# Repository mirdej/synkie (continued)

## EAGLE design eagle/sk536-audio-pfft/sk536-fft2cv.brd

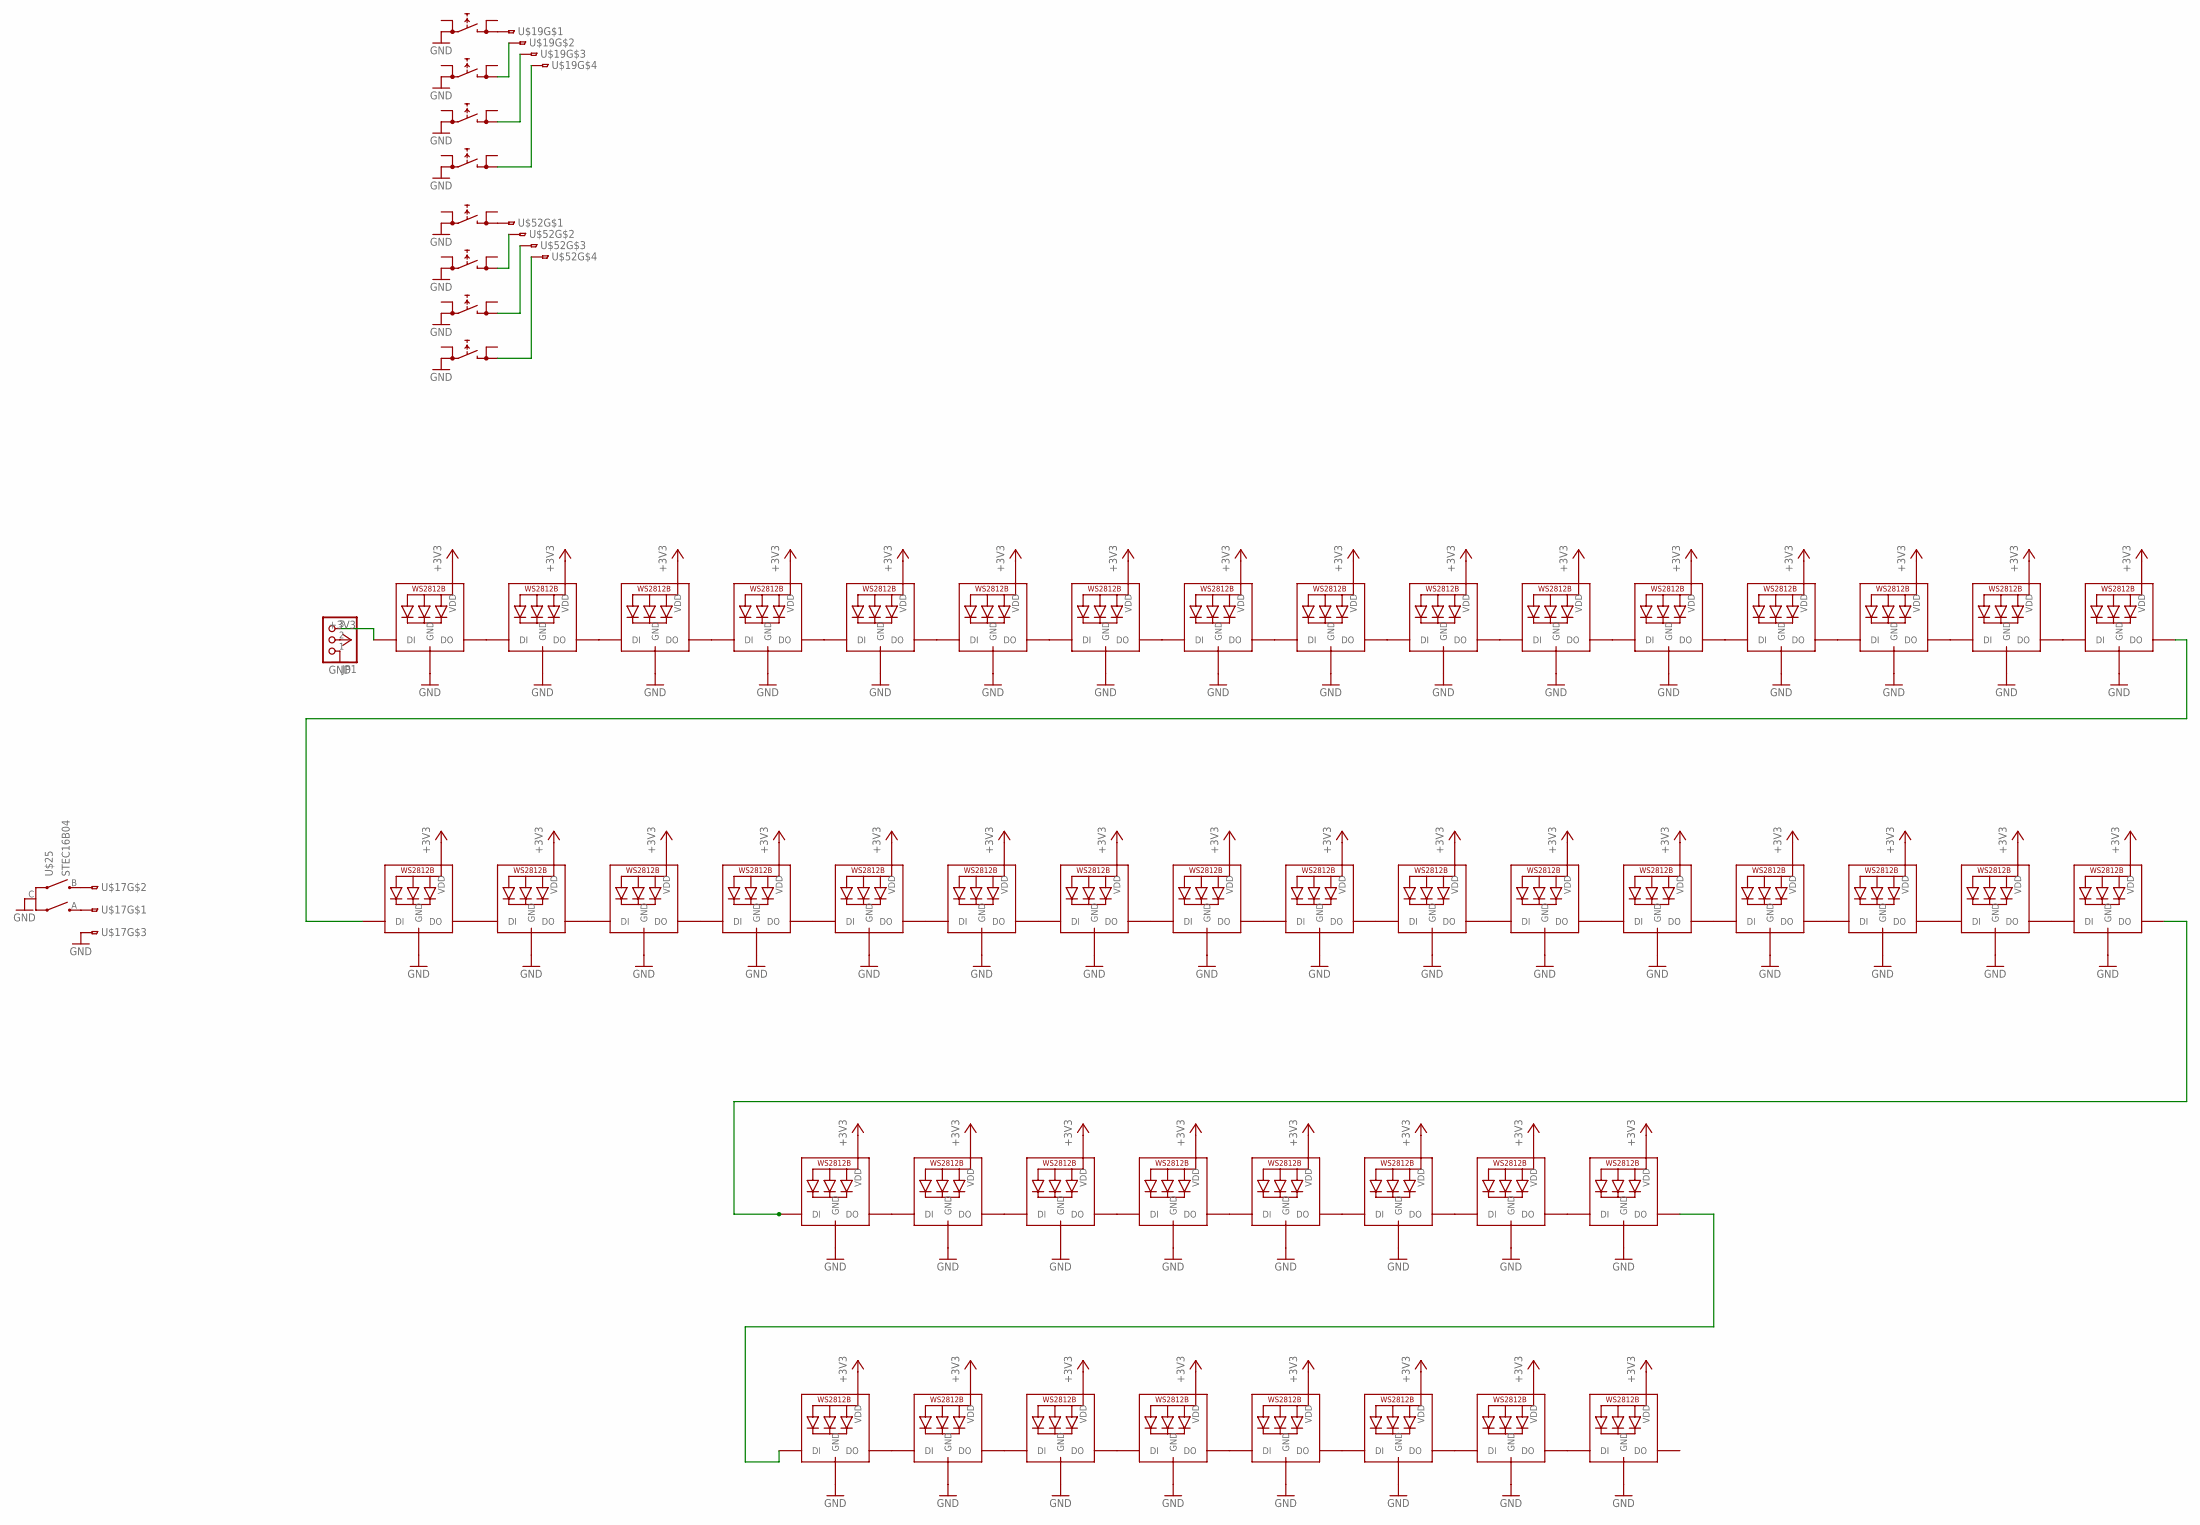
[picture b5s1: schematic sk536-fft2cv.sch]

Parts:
JP1: PINHD-1X3; 1X03
T1, T2, T3, T4, T5, T6, T7, T8: PRINTTASTER_SMDALPS-SKQ; SKQGAKE010
U$1, U$2, U$3, U$4, U$5, U$6, U$7, U$8, U$9, U$10, U$11, U$12, U$13, U$14, U$15, U$16, U$18, U$20, U$21, U$22, U$23, U$24, U$26, U$27, U$28, U$29, U$30, U$31, U$32, U$33, U$34, U$35, U$36, U$37, U$38, U$39, U$40, U$41, U$42, U$43, U$44, U$45, U$46, U$47, U$48, U$49, U$50, U$51: SK6812MINI
U$17: 3PIN-SMD-2.54
U$19, U$52: 4PIN-SMD; 4PIN-SMD-2.54
U$25: STEC16B04

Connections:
+3V3: JP1.2, U$1.4 (VDD), U$2.4 (VDD), U$3.4 (VDD), U$4.4 (VDD), U$5.4 (VDD), U$6.4 (VDD), U$7.4 (VDD), U$8.4 (VDD), U$9.4 (VDD), U$10.4 (VDD), U$11.4 (VDD), U$12.4 (VDD), U$13.4 (VDD), U$14.4 (VDD), U$15.4 (VDD), U$16.4 (VDD), U$18.4 (VDD), U$20.4 (VDD), U$21.4 (VDD), U$22.4 (VDD), U$23.4 (VDD), U$24.4 (VDD), U$26.4 (VDD), U$27.4 (VDD), U$28.4 (VDD), U$29.4 (VDD), U$30.4 (VDD), U$31.4 (VDD), U$32.4 (VDD), U$33.4 (VDD), U$34.4 (VDD), U$35.4 (VDD), U$36.4 (VDD), U$37.4 (VDD), U$38.4 (VDD), U$39.4 (VDD), U$40.4 (VDD), U$41.4 (VDD), U$42.4 (VDD), U$43.4 (VDD), U$44.4 (VDD), U$45.4 (VDD), U$46.4 (VDD), U$47.4 (VDD), U$48.4 (VDD), U$49.4 (VDD), U$50.4 (VDD), U$51.4 (VDD)
GND: JP1.1, T1.2 (0), T2.2 (0), T3.2 (0), T4.2 (0), T5.2 (0), T6.2 (0), T7.2 (0), T8.2 (0), U$1.2 (GND), U$2.2 (GND), U$3.2 (GND), U$4.2 (GND), U$5.2 (GND), U$6.2 (GND), U$7.2 (GND), U$8.2 (GND), U$9.2 (GND), U$10.2 (GND), U$11.2 (GND), U$12.2 (GND), U$13.2 (GND), U$14.2 (GND), U$15.2 (GND), U$16.2 (GND), U$17.3, U$18.2 (GND), U$20.2 (GND), U$21.2 (GND), U$22.2 (GND), U$23.2 (GND), U$24.2 (GND), U$25.C, U$26.2 (GND), U$27.2 (GND), U$28.2 (GND), U$29.2 (GND), U$30.2 (GND), U$31.2 (GND), U$32.2 (GND), U$33.2 (GND), U$34.2 (GND), U$35.2 (GND), U$36.2 (GND), U$37.2 (GND), U$38.2 (GND), U$39.2 (GND), U$40.2 (GND), U$41.2 (GND), U$42.2 (GND), U$43.2 (GND), U$44.2 (GND), U$45.2 (GND), U$46.2 (GND), U$47.2 (GND), U$48.2 (GND), U$49.2 (GND), U$50.2 (GND), U$51.2 (GND)
unnamed: U$1.1 (DO), U$2.3 (DI)
unnamed: U$2.1 (DO), U$3.3 (DI)
unnamed: U$3.1 (DO), U$4.3 (DI)
unnamed: U$4.1 (DO), U$5.3 (DI)
unnamed: U$5.1 (DO), U$6.3 (DI)
unnamed: U$6.1 (DO), U$7.3 (DI)
unnamed: U$7.1 (DO), U$8.3 (DI)
unnamed: U$8.1 (DO), U$9.3 (DI)
unnamed: U$9.1 (DO), U$10.3 (DI)
unnamed: U$10.1 (DO), U$11.3 (DI)
unnamed: U$13.1 (DO), U$14.3 (DI)
unnamed: U$14.1 (DO), U$15.3 (DI)
unnamed: U$15.1 (DO), U$16.3 (DI)
unnamed: U$11.1 (DO), U$12.3 (DI)
unnamed: U$12.1 (DO), U$13.3 (DI)
unnamed: U$26.1 (DO), U$27.3 (DI)
unnamed: U$27.1 (DO), U$28.3 (DI)
unnamed: U$28.1 (DO), U$29.3 (DI)
unnamed: U$29.1 (DO), U$30.3 (DI)
unnamed: U$30.1 (DO), U$31.3 (DI)
unnamed: U$31.1 (DO), U$32.3 (DI)
unnamed: U$32.1 (DO), U$33.3 (DI)
unnamed: U$33.1 (DO), U$34.3 (DI)
unnamed: U$34.1 (DO), U$35.3 (DI)
unnamed: U$35.1 (DO), U$36.3 (DI)
unnamed: U$38.1 (DO), U$39.3 (DI)
unnamed: U$39.1 (DO), U$40.3 (DI)
unnamed: U$40.1 (DO), U$41.3 (DI)
unnamed: U$36.1 (DO), U$37.3 (DI)
unnamed: U$37.1 (DO), U$38.3 (DI)
unnamed: U$16.1 (DO), U$26.3 (DI)
unnamed: U$18.3 (DI), U$41.1 (DO)
unnamed: U$18.1 (DO), U$20.3 (DI)
unnamed: U$20.1 (DO), U$21.3 (DI)
unnamed: U$23.1 (DO), U$24.3 (DI)
unnamed: U$24.1 (DO), U$42.3 (DI)
unnamed: U$42.1 (DO), U$43.3 (DI)
unnamed: U$21.1 (DO), U$22.3 (DI)
unnamed: U$22.1 (DO), U$23.3 (DI)
unnamed: U$17.1, U$25.A
unnamed: U$44.1 (DO), U$45.3 (DI)
unnamed: U$45.1 (DO), U$46.3 (DI)
unnamed: U$48.1 (DO), U$49.3 (DI)
unnamed: U$49.1 (DO), U$50.3 (DI)
unnamed: U$50.1 (DO), U$51.3 (DI)
unnamed: U$46.1 (DO), U$47.3 (DI)
unnamed: U$47.1 (DO), U$48.3 (DI)
unnamed: U$43.1 (DO), U$44.3 (DI)
unnamed: U$17.2, U$25.B
unnamed: JP1.3, U$1.3 (DI)
unnamed: T1.4 (1), U$19.1
unnamed: T2.4 (1), U$19.2
unnamed: T3.4 (1), U$19.3
unnamed: T4.4 (1), U$19.4
unnamed: T5.4 (1), U$52.1
unnamed: T6.4 (1), U$52.2
unnamed: T7.4 (1), U$52.3
unnamed: T8.4 (1), U$52.4

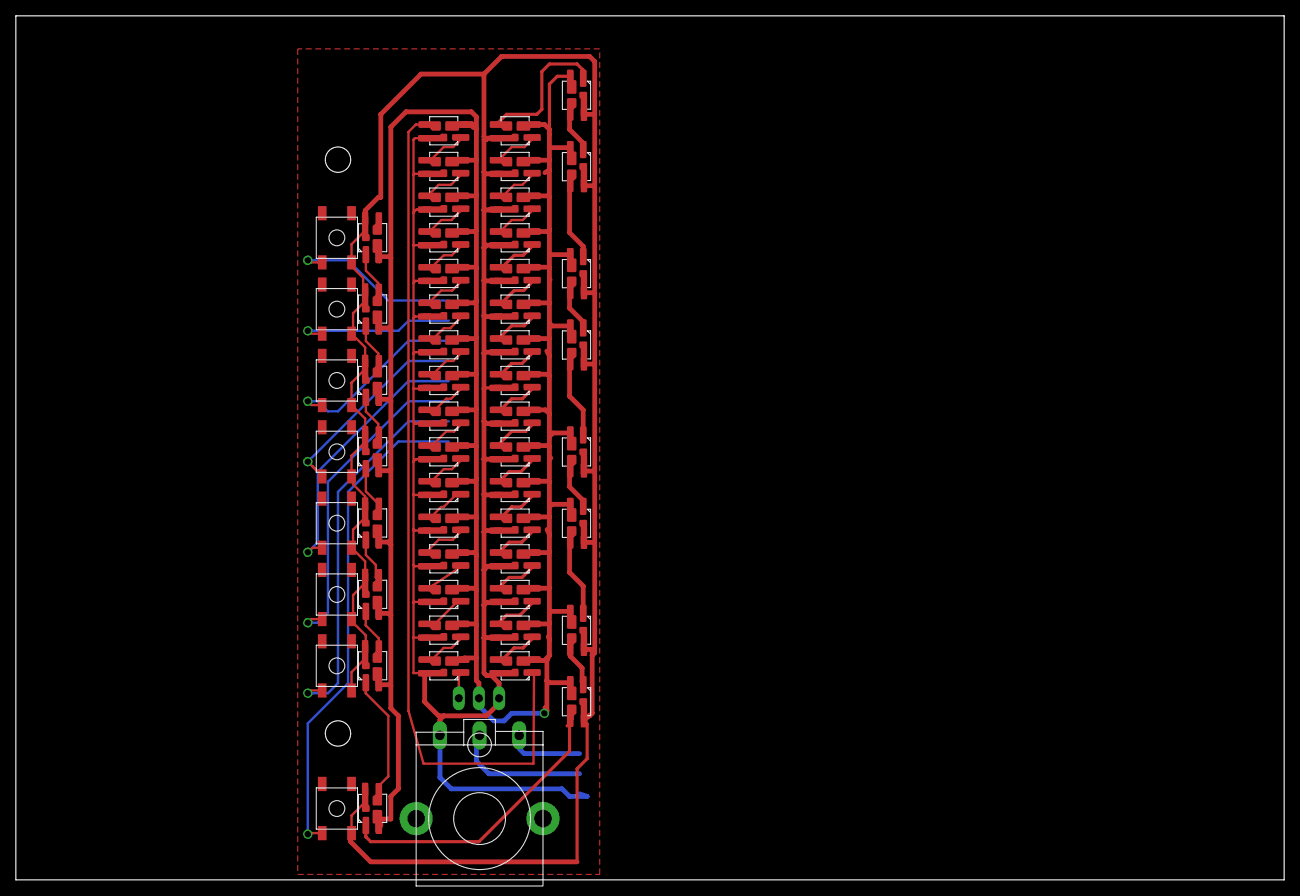
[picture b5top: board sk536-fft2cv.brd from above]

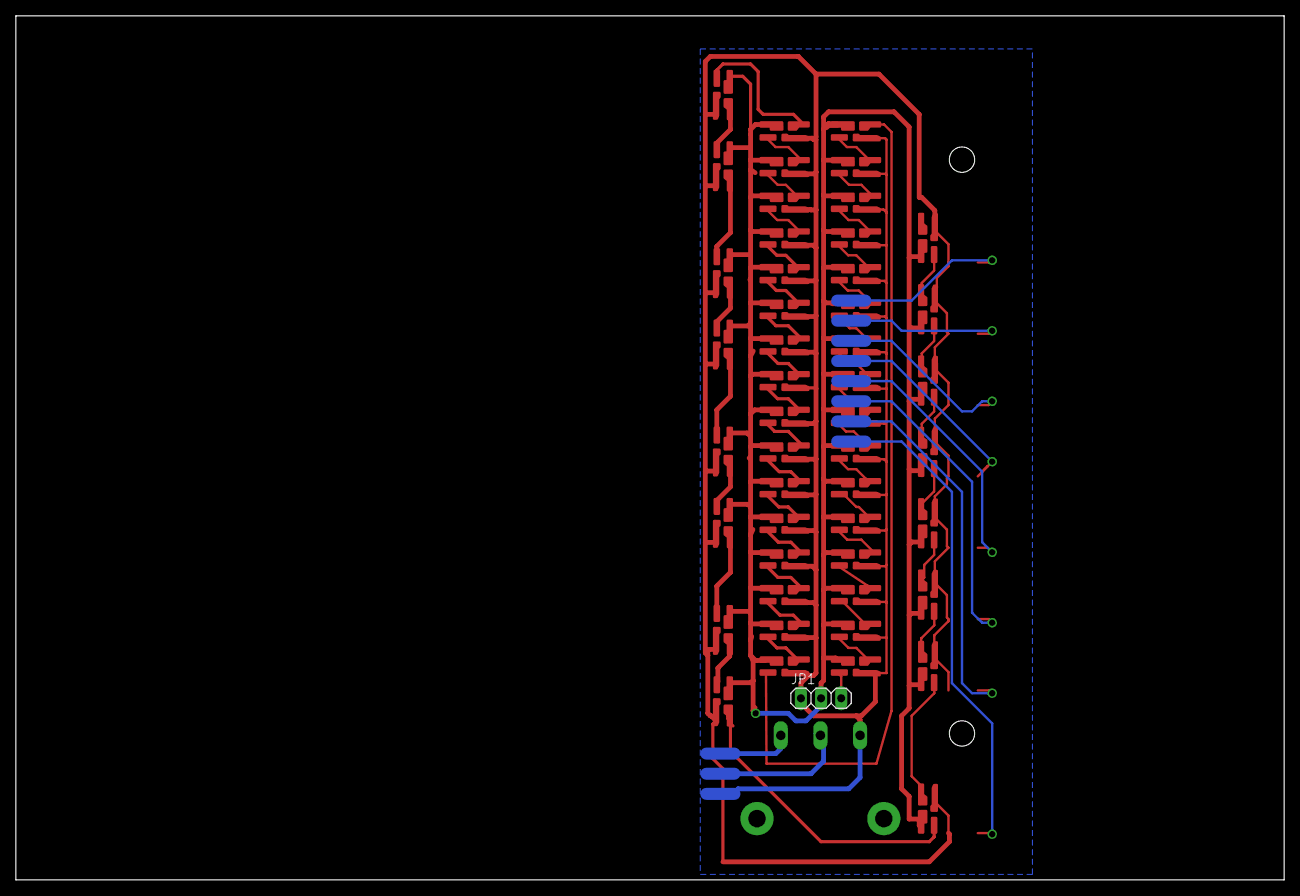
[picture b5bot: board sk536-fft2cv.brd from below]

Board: 2 copper layers, 160.0 x 109.0 mm, 61 parts (4 on the bottom side), 60 nets.

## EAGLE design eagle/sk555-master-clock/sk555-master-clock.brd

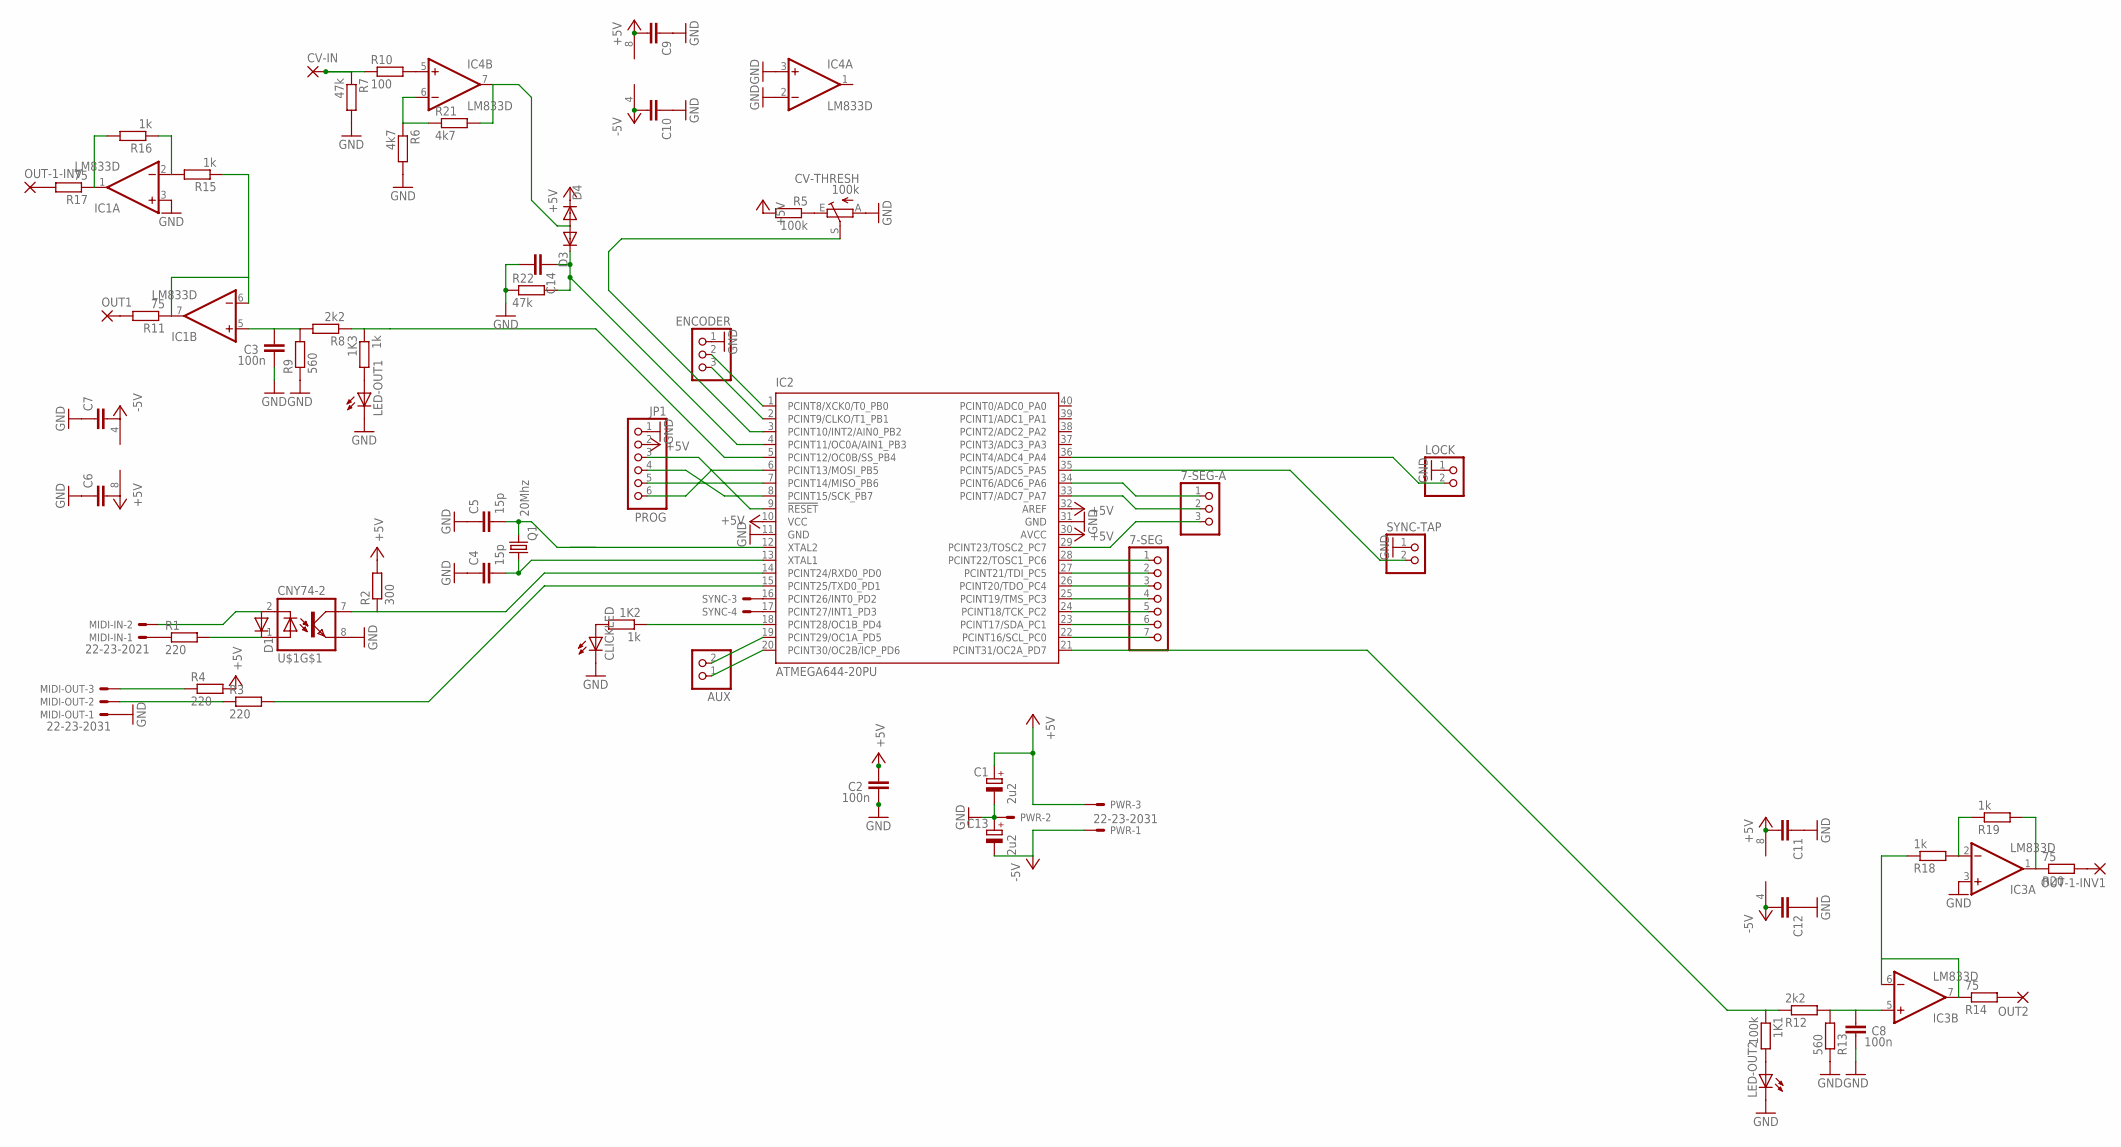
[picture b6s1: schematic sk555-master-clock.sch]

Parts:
1K1: 100k; R1206
1K2, 1K3: 1k; R1206
7-SEG: PINHD-1X7; 1X07
7-SEG-A: PINHD-1X3; 1X03
AUX: PINHD-1X2; 1X02
C1, C13: 2u2; CT3528
C2, C3, C8: 100n; C0805
C4, C5: 15p; C1206
C6, C7, C9, C10, C14: C-EUC1206; C1206
C11, C12: C-EUC0805; C0805
CLICKLED: LED3MM
CV-IN: 3,17/1,1
CV-THRESH: 100k; CIP20C-6MM
D1, D3, D4: DIODE-MINIMELF; MINIMELF
ENCODER: PINHD-1X3; 1X03
IC1, IC3, IC4: LM833D; SO08
IC2: ATMEGA644-20PU; DIL40
JP1: PROG; 1X06
LED-OUT1, LED-OUT2: LED3MM
LOCK: PINHD-1X2; 1X02
MIDI-IN: 22-23-2021
MIDI-OUT: 22-23-2031
OUT1, OUT2: 3,17/1,1
OUT-1-INV, OUT-1-INV1: 3,17/1,1
PWR: 22-23-2031
Q1: 20Mhz; HC49UP
R1, R3, R4: 220; R1206
R2: 300; R1206
R5: 100k; R1206
R6, R21: 4k7; R1206
R7, R22: 47k; R1206
R8, R12: 2k2; R1206
R9, R13: 560; R1206
R10: 100; R1206
R11, R14, R17, R20: 75; R1206
R15, R16, R18, R19: 1k; R1206
SYNC: 22-23-2041
SYNC-TAP: PINHD-1X2; 1X02
U$1: CNY74-2; DIL08

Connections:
+5V: C1.+, C2.1, C6.2, C9.2, C11.2, D4.C, IC1.8 (V+), IC2.10 (VCC), IC2.30 (AVCC), IC2.32 (AREF), IC3.8 (V+), IC4.8 (V+), JP1.2, PWR.3, R2.2, R4.2, R5.2
-5V: C7.2, C10.2, C12.2, C13.-, IC1.4 (V-), IC3.4 (V-), IC4.4 (V-), PWR.1
GND: C1.-, C2.2, C3.2, C4.1, C5.1, C6.1, C7.1, C8.2, C9.1, C10.1, C11.1, C12.1, C13.+, C14.2, CLICKLED.K (C), CV-THRESH.A, ENCODER.1, IC1.3 (+IN), IC2.11 (GND), IC2.31 (GND), IC3.3 (+IN), IC4.2 (-IN), IC4.3 (+IN), JP1.1, LED-OUT1.K (C), LED-OUT2.K (C), LOCK.1, MIDI-OUT.1, PWR.2, R6.2, R7.2, R9.1, R13.1, R22.1, SYNC-TAP.1, U$1.8 (EMI)
unnamed: IC2.8 (PCINT15/SCK_PB7), JP1.4
unnamed: IC2.7 (PCINT14/MISO_PB6), JP1.5
unnamed: IC2.6 (PCINT13/MOSI_PB5), JP1.6
unnamed: IC2.9 (!RESET), JP1.3
unnamed: C4.2, IC2.13 (XTAL1), Q1.1
unnamed: MIDI-IN.1, R1.1
unnamed: D1.A, MIDI-IN.2, U$1.2 (C)
unnamed: D1.C, R1.2, U$1.1 (A)
unnamed: IC2.14 (PCINT24/RXD0_PD0), R2.1, U$1.7 (COL)
unnamed: MIDI-OUT.2, R3.1
unnamed: MIDI-OUT.3, R4.1
unnamed: IC2.15 (PCINT25/TXD0_PD1), R3.2
unnamed: CV-IN.1, R7.1, R10.1
unnamed: OUT-1-INV.1, R17.2
unnamed: CV-THRESH.S, IC2.3 (PCINT10/INT2/AIN0_PB2)
unnamed: CV-THRESH.E, R5.1
unnamed: C14.1, D3.C, IC2.4 (PCINT11/OC0A/AIN1_PB3), R22.2
unnamed: OUT1.1, R11.2
unnamed: IC4.5 (+IN), R10.2
unnamed: IC4.6 (-IN), R6.1, R21.1
unnamed: IC2.36 (PCINT4/ADC4_PA4), LOCK.2
unnamed: IC2.35 (PCINT5/ADC5_PA5), SYNC-TAP.2
unnamed: 1K3.1, IC2.5 (PCINT12/OC0B/SS_PB4), R8.1
unnamed: OUT-1-INV1.1, R20.2
unnamed: 1K3.2, LED-OUT1.A
unnamed: IC2.16 (PCINT26/INT0_PD2), SYNC.3
unnamed: IC2.17 (PCINT27/INT1_PD3), SYNC.4
unnamed: IC1.2 (-IN), R15.2, R16.1
unnamed: C3.1, IC1.5 (+IN), R8.2, R9.2
unnamed: IC1.6 (-IN), IC1.7 (OUT), R11.1, R15.1
unnamed: 1K1.1, IC2.21 (PCINT31/OC2A_PD7), R12.1
unnamed: OUT2.1, R14.2
unnamed: 7-SEG.1, IC2.28 (PCINT22/TOSC1_PC6)
unnamed: C8.1, IC3.5 (+IN), R12.2, R13.2
unnamed: IC3.6 (-IN), IC3.7 (OUT), R14.1, R18.1
unnamed: C5.2, IC2.12 (XTAL2), Q1.2
unnamed: 1K1.2, LED-OUT2.A
unnamed: IC3.2 (-IN), R18.2, R19.1
unnamed: IC3.1 (OUT), R19.2, R20.1
unnamed: 7-SEG.2, IC2.27 (PCINT21/TDI_PC5)
unnamed: 7-SEG.3, IC2.26 (PCINT20/TDO_PC4)
unnamed: 7-SEG.4, IC2.25 (PCINT19/TMS_PC3)
unnamed: 7-SEG.5, IC2.24 (PCINT18/TCK_PC2)
unnamed: 7-SEG.6, IC2.23 (PCINT17/SDA_PC1)
unnamed: 7-SEG.7, IC2.22 (PCINT16/SCL_PC0)
unnamed: 7-SEG-A.3, IC2.29 (PCINT23/TOSC2_PC7)
unnamed: 7-SEG-A.2, IC2.33 (PCINT7/ADC7_PA7)
unnamed: 7-SEG-A.1, IC2.34 (PCINT6/ADC6_PA6)
unnamed: 1K2.2, CLICKLED.A
unnamed: 1K2.1, IC2.18 (PCINT28/OC1B_PD4)
unnamed: AUX.1, IC2.20 (PCINT30/OC2B/ICP_PD6)
unnamed: AUX.2, IC2.19 (PCINT29/OC1A_PD5)
unnamed: ENCODER.2, IC2.1 (PCINT8/XCK0/T0_PB0)
unnamed: ENCODER.3, IC2.2 (PCINT9/CLKO/T1_PB1)
unnamed: D3.A, D4.A, IC4.7 (OUT), R21.2
unnamed: IC1.1 (OUT), R16.2, R17.1

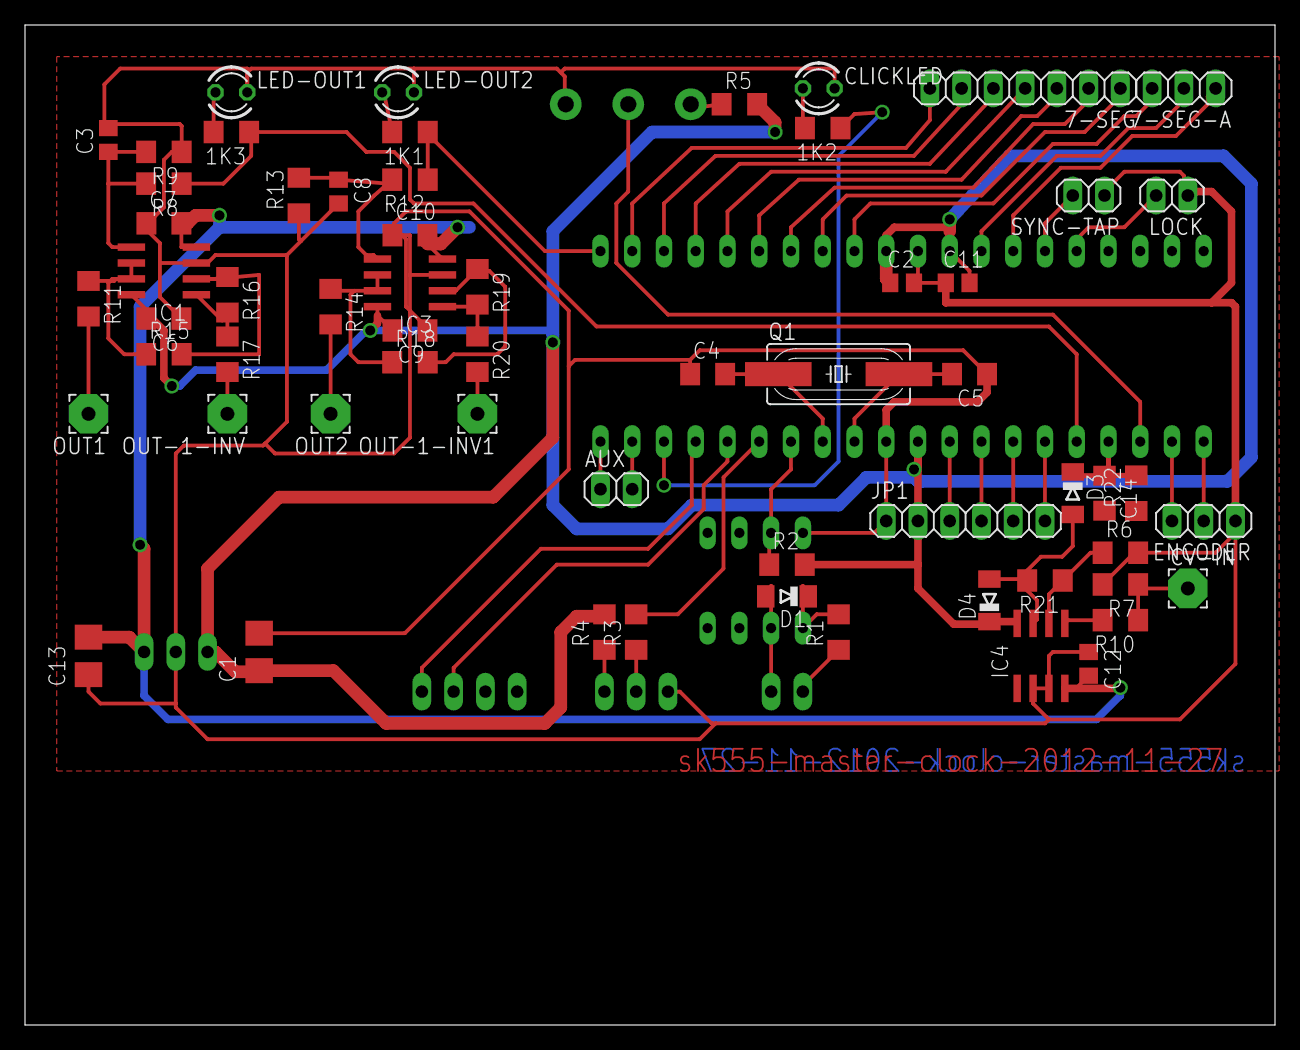
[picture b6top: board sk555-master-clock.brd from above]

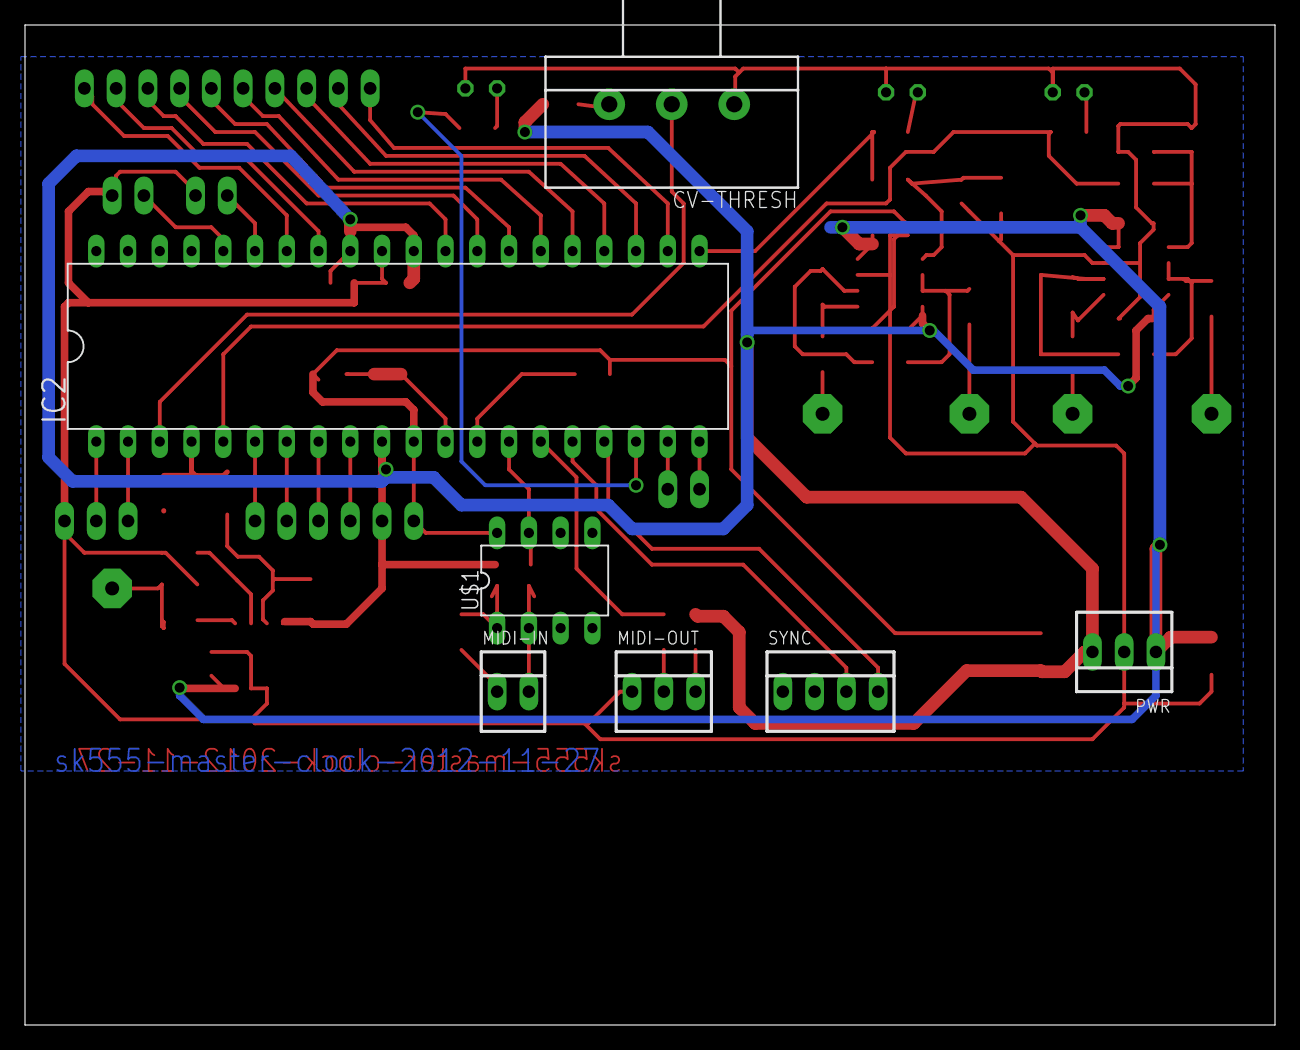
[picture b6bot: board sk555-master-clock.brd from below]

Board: 2 copper layers, 100.0 x 80.0 mm, 68 parts (7 on the bottom side), 59 nets.

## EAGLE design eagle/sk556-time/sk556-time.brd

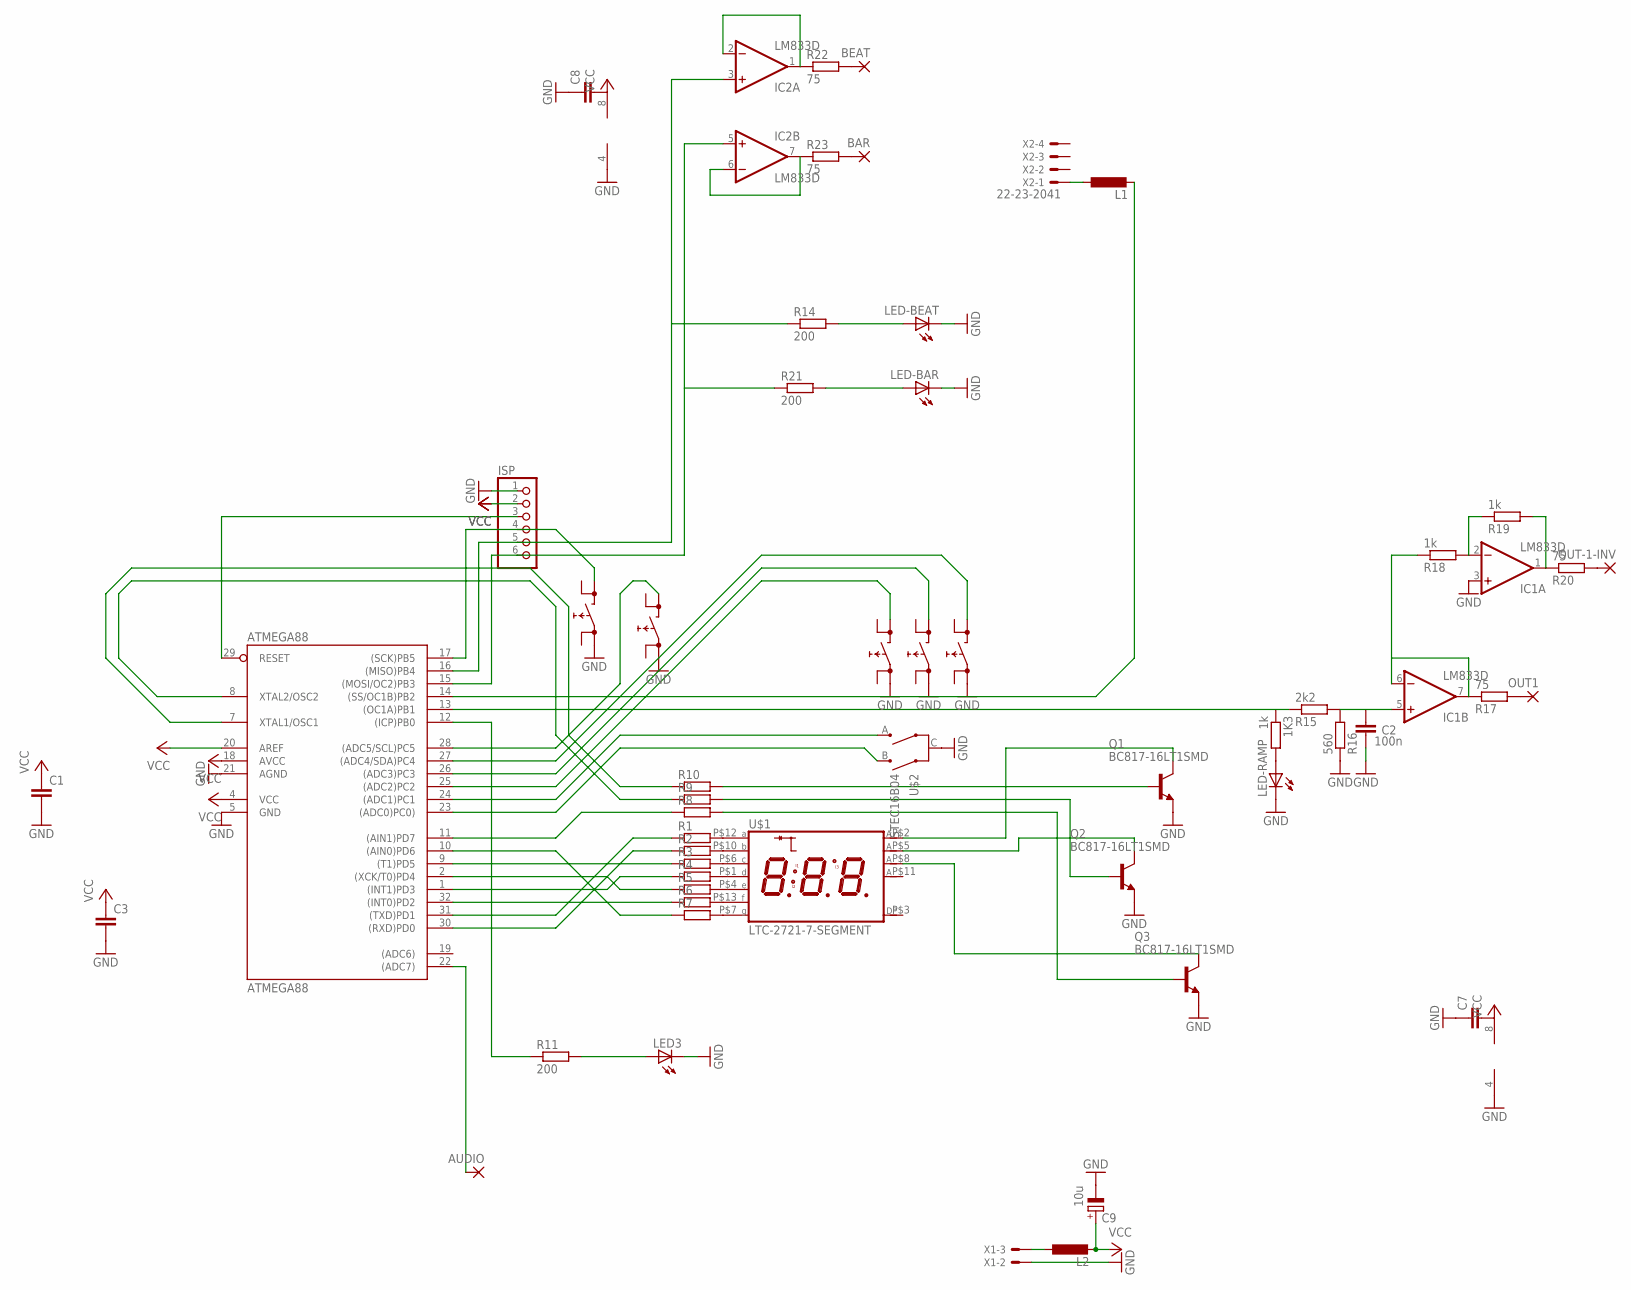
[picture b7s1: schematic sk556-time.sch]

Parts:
1K3: 1k; R1206
ATMEGA88: ATMEGA88; TQFP32-08
AUDIO: 3,17/1,1
BAR: 3,17/1,1
BEAT: 3,17/1,1
C1, C3, C7: C-EUC0603; C0603
C2: 100n; C0805
C8: C-EUC1206; C1206
C9: 10u; CT3528
IC1, IC2: LM833D; SO08
ISP: PINHD-1X6; 1X06
L1, L2: L-EUL5038P; L5038P
LED3: LEDCHIPLED_1206; CHIPLED_1206
LED-BAR: LEDCHIPLED_1206; CHIPLED_1206
LED-BEAT: LEDCHIPLED_1206; CHIPLED_1206
LED-RAMP: LEDCHIPLED_1206; CHIPLED_1206
LEFT: PRINTTASTER_SMD; SMD_SWITCH
LOOPER: PRINTTASTER_SMD; SMD_SWITCH
MIDDLE: PRINTTASTER_SMD; SMD_SWITCH
OUT1: 3,17/1,1
OUT-1-INV: 3,17/1,1
Q1, Q2, Q3: BC817-16LT1SMD; SOT23-BEC
R1, R2, R3, R4, R5, R6, R7, R8, R9, R10: R-EU_R1206; R1206
R11, R14, R21: 200; R1206
R15: 2k2; R1206
R16: 560; R1206
R17, R20, R22, R23: 75; R1206
R18, R19: 1k; R1206
RIGHT: PRINTTASTER_SMD; SMD_SWITCH
TAP: PRINTTASTER_SMD; SMD_SWITCH
U$1: LTC-2721-7-SEGMENT; LTC-2721
U$2: STEC16B04
X1: 22-23-2031
X2: 22-23-2041

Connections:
GND: ATMEGA88.5 (GND), ATMEGA88.21 (AGND), C1.2, C2.2, C3.2, C7.1, C8.1, C9.-, IC1.3 (+IN), IC1.4 (V-), IC2.4 (V-), ISP.1, LED3.C, LED-BAR.C, LED-BEAT.C, LED-RAMP.C, LEFT.AA (0), LOOPER.AA (0), MIDDLE.AA (0), Q1.E, Q2.E, Q3.E, R16.1, RIGHT.AA (0), TAP.AA (0), U$2.C, X1.2
MISO: ATMEGA88.16 ((MISO)PB4), IC2.3 (+IN), ISP.5, R14.1
MOSI: ATMEGA88.15 ((MOSI/OC2)PB3), IC2.5 (+IN), ISP.6, R21.1
unnamed: ATMEGA88.30 ((RXD)PD0), R2.1
unnamed: ATMEGA88.31 ((TXD)PD1), R1.1
unnamed: ATMEGA88.32 ((INT0)PD2), R6.1
unnamed: ATMEGA88.1 ((INT1)PD3), R4.1
unnamed: ATMEGA88.2 ((XCK/T0)PD4), R5.1
unnamed: ATMEGA88.8 (XTAL2/OSC2), R9.1
unnamed: ATMEGA88.7 (XTAL1/OSC1), R10.1
unnamed: ATMEGA88.11 ((AIN1)PD7), R8.1
unnamed: ATMEGA88.9 ((T1)PD5), R3.1
unnamed: R1.2, U$1.P$12 (A)
unnamed: R2.2, U$1.P$10 (B)
unnamed: R3.2, U$1.P$6 (C)
unnamed: R4.2, U$1.P$1 (D)
unnamed: R5.2, U$1.P$4 (E)
unnamed: R6.2, U$1.P$13 (F)
unnamed: R7.2, U$1.P$7 (G)
unnamed: ATMEGA88.29 (RESET), ISP.3
unnamed: ATMEGA88.22 ((ADC7)), AUDIO.1
unnamed: C7.2, IC1.8 (V+)
unnamed: ATMEGA88.14 ((SS/OC1B)PB2), L1.2
unnamed: L1.1, X2.1
unnamed: ATMEGA88.10 ((AIN0)PD6), R7.1
unnamed: ATMEGA88.23 ((ADC0)PC0)), U$2.B
unnamed: ATMEGA88.24 ((ADC1)PC1), U$2.A
unnamed: Q1.B, R10.2
unnamed: Q2.B, R9.2
unnamed: Q3.B, R8.2
unnamed: Q1.C, U$1.P$2 (D1)
unnamed: Q2.C, U$1.P$5 (D2)
unnamed: Q3.C, U$1.P$8 (D3)
unnamed: ATMEGA88.25 ((ADC2)PC2), RIGHT.BB (1)
unnamed: ATMEGA88.26 ((ADC3)PC3), MIDDLE.BB (1)
unnamed: ATMEGA88.27 ((ADC4/SDA)PC4), LEFT.BB (1)
unnamed: LED-BEAT.A, R14.2
unnamed: ATMEGA88.28 ((ADC5/SCL)PC5), LOOPER.BB (1)
unnamed: ATMEGA88.12 ((ICP)PB0), R11.1
unnamed: LED-BAR.A, R21.2
unnamed: IC2.1 (OUT), IC2.2 (-IN), R22.1
unnamed: 1K3.1, ATMEGA88.13 ((OC1A)PB1), R15.1
unnamed: C2.1, IC1.5 (+IN), R15.2, R16.2
unnamed: IC1.6 (-IN), IC1.7 (OUT), R17.1, R18.1
unnamed: 1K3.2, LED-RAMP.A
unnamed: IC1.2 (-IN), R18.2, R19.1
unnamed: OUT-1-INV.1, R20.2
unnamed: OUT1.1, R17.2
unnamed: BEAT.1, R22.2
unnamed: IC2.6 (-IN), IC2.7 (OUT), R23.1
unnamed: BAR.1, R23.2
unnamed: L2.1, X1.3
unnamed: IC1.1 (OUT), R19.2, R20.1
unnamed: LED3.A, R11.2
SCK: ATMEGA88.17 ((SCK)PB5), ISP.4, TAP.BB (1)
VCC: ATMEGA88.4 (VCC), ATMEGA88.18 (AVCC), ATMEGA88.20 (AREF), C1.1, C3.1, C8.2, C9.+, IC2.8 (V+), ISP.2, L2.2

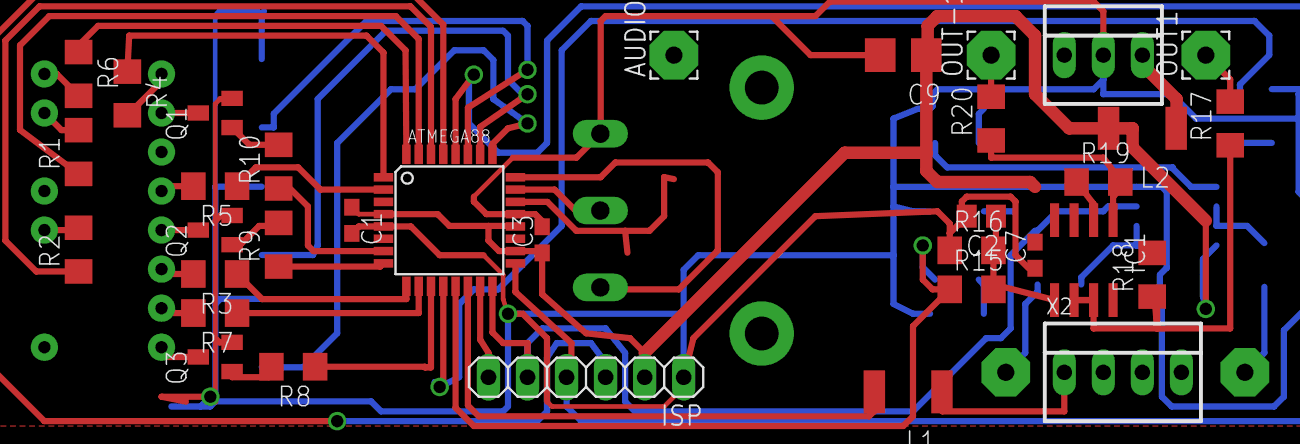
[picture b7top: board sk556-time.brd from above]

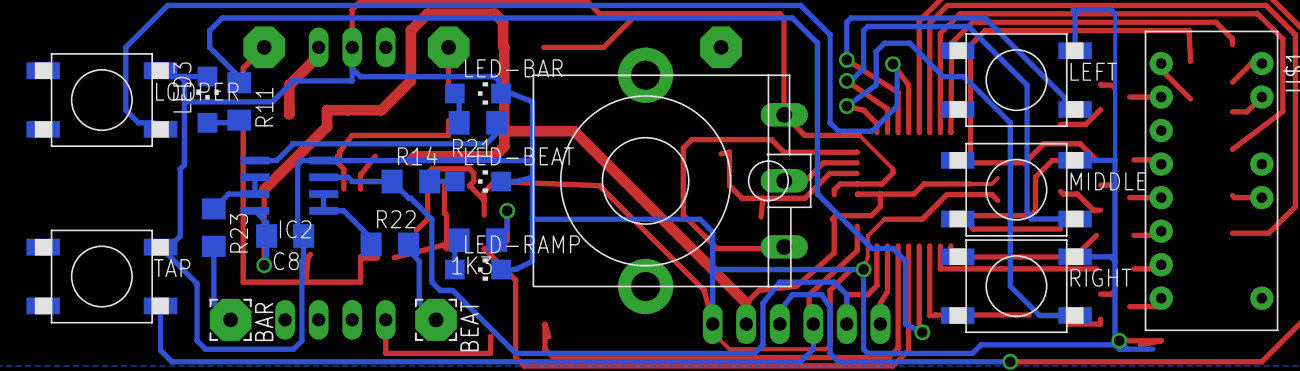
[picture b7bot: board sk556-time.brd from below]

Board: 2 copper layers, 55 parts (21 on the bottom side), 56 nets.
